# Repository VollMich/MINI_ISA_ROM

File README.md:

# MINI_ISA_ROM Card

the original design is from wiretap and it is awesome! He published it a while ago in a [thread on vogons](https://www.vogons.org/viewtopic.php?t=82499). Please do not get confused by my explanations further down. You don't need to understand binary logic to use this Rom adapter card. All you need to know is, that this is an exact copy of his design, except for the Jumper settings table on the silk screen , which has been corrected on this PCB, since wiretap's Jumper settings table was wrong. This PCB can be set according to the table on the card. This was the whole reason for this variant of wiretap's original design. You also need to know: Wiretap's original design is flawless and can be used without problems. It's just the settings table on the silk screen, that can give you a headache. You can use the jumper settings table from this project, to set up wiretap's card and you'll be fine. If you prefer to build a new one with a corrected silk screen, feel free to [download my gerbers](https://github.com/VollMich/MINI_ISA_ROM/raw/main/gerbers.zip).

## Why did i modify wiretap's awsome pcb design?
Wiretap's design is flawless except for the jumper table on the silk screen, which doesn't show the correct settings for the card. But his card works great otherwise. I built this version of his PCB to supply it with a proper silk screen. The complete list of possible Adresses is as follows:

|J1-J4|Base Address| Range | Validity | Usable? | Comment |
|-----|------------|-------|----------|---------|---------|
|0000|F800| F8000-FFFFF | INVALID | too high for option rom, DO NOT USE!||
|1000|F000| F0000-F7FFF | INVALID | too high for option rom, DO NOT USE!||
|0100|E800| E8000-EFFFF | INVALID | too high for option rom, DO NOT USE!||
|1100|E000| E0000-E7FFF | INVALID | too high for option rom, DO NOT USE!||
|**0010**|**D800**| **D8000-DFFFF** | **VALID**   | valid 32K block for a 27C256 Rom    || 
|**1010**|**D000**| **D0000-D7FFF** | **VALID**   | valid 32K block for a 27C256 Rom    ||
|**0110**|**C800**| **C8000-CFFFF** | **VALID**   | valid 32K block for a 27C256 Rom    | If you happen to have built AnotherMaker's version of this PCB, be aware, that there is a signal line missing between J2 on his PCB, this setting doesn't work on his card| 
|**1110**|**C000**| **C0000-C7FFF** | **VALID**   | valid 32K block for a 27C256 Rom    | VGA roms often start at C000. If you have a VGA card in your system, this range is probably occupied. If you happen to have built AnotherMaker's version of this PCB, be aware, that there is a signal line missing between J2 on his PCB, this setting doesn't work on his card.|  
|0001|B800| B8000-BFFFF | INVALID | too low for option rom, DO NOT USE! ||
|1001|B000| B0000-B7FFF | INVALID | too low for option rom, DO NOT USE! ||
|0101|A800| A8000-AFFFF | INVALID | too low for option rom, DO NOT USE! ||
|1101|A000| A0000-A7FFF | INVALID | too low for option rom, DO NOT USE! ||
|0011|9800| 98000-9FFFF | INVALID | too low for option rom, DO NOT USE! ||
|1011|9000| 90000-97FFF | INVALID | too low for option rom, DO NOT USE! ||
|0111|8800| 88000-8FFFF | INVALID | too low for option rom, DO NOT USE! ||
|1111|8000| 80000-87FFF | INVALID | too low for option rom, DO NOT USE! ||

There are really just four valid jumper settings out of sixteen possible combinations. All the other addresses wouldn't be recognized as option roms or even cause address conflicts with other resources. The reason is the huge rom size of 32K and the designers choice, to map the full size of the rom. The rom is directly attached to ADR0-ADR14 (which is 32K). With this low number of parts, it was kind of mandatory to use ADR15-ADR18 for address comparison. But only four combinations of J1-J4 wich are used to compare to ADR15-ADR18 end up in the address range for option roms, which is only 128K. There are only four 32K blocks possible in this range. Other cards can set more addresses, because they use smaller roms and hence, smaller blocks like 16K, 8K or even smaller. With this card you can use only one of four valid 32K blocks between C000 and DFFF. 

these are: 

|J1-J4|Base Address| Range | Block size |
|-----|------------|-------|------------|
|**0010**|**D800**| **D8000-DFFFF** | 32K|
|**1010**|**D000**| **D0000-D7FFF** | 32K|
|**0110**|**C800**| **C8000-CFFFF** | 32K|
|**1110**|**C000**| **C0000-C7FFF** | 32K|

## How does the address selection work?
The rom is directly connected to ADR0-ADR14 (32K). The Jumpers pins in the jumper block on this card are connected to ADR15-ADR18 left to right. The msb is on the right. The pins are pulled up to 5V by the 10K resistor network. If you set a jumper, the line is pulled down to 0V. The jumpers are connected as follows:

| Jumper (upper pin)| Signal Name| Connected to...| Used for...| Comment |
|-------------------|-----------|----------------|-------------|---------|
|J1                | P0        | 47LS688-PIN2   | pulled up via resistor network, to be compared to ADR15||
|J2                | P1        | 47LS688-PIN4   | pulled up via resistor network, to be compared to ADR16| Watch out if you got hold of AnotherMaker's version of this PCB on PCBWay. This line is missing on his layout, J2 is useless on his card.|
|J3                | P2        | 47LS688-PIN6   | pulled up via resistor network, to be compared to ADR17||
|J4                | P3        | 47LS688-PIN8   | pulled up via resistor network, to be compared to ADR18||

## OK, give me an example
This is the Address C0000, the base address of the memory range for option roms. It's binary representation is: 1100 0000 0000 0000 0000. if you write C0000 differently you get: 1 1000 000000000000000. The four separated bits on the left are connected to the jumper block from right to left. If you read it from right to left, you get 0001. There is one more step to do. You need to invert the value because a set jumper pulls the bit low. It's inverse logic. 
You get 1110. Hooray, this is the jumper setting for C0000.

## On writing a rom to this huge 32K chip (27C256). 
---------------------------------------------------------------------------------
If you just want to write a single rom to your chip, you can do so. Just make sure that your rom is aligned properly. Every rom has a header which contains the length of the rom. The length of the rom must be a multiple of 2K (it's 512B but there are some motherboards, that need the rom size to be a multiple of 2K, so it's best practice to follow this rule). If you downloaded a rom from xtide, it's probably not aligned. At least current binary downloads aren't. You need to run XTIDECFG.EXE to align the rom properly. The tool will pump up the size to the next 2K-border and calculate a proper 3-byte checksum at the end of the rom. Remember that you need to use the version of XTIDECFG.EXE, that was supplied with your roms. If you save the rom to a file, it is ready to be written with your eprom writer. When you are loading the file into your writer, you can select "Clear buffer when loading the file: Clear buffer with 0x00". The checksum does not have to be calculated again. The zeros at the end of the rom will be seen by your system and the range will be occupied, but only the first, properly aligned and properly checksummed area will be recognized as rom. And it will work fine. 

## On writing multiple roms on one chip
No one can stop you from loading multiple roms into the 32K of the 27c256. As long as you align them on 2K-adresses and supply the images with the correct headers and checksums, they will each be recognized as separate rom without a problem.

Happy retrocomputing ;)

Phonox

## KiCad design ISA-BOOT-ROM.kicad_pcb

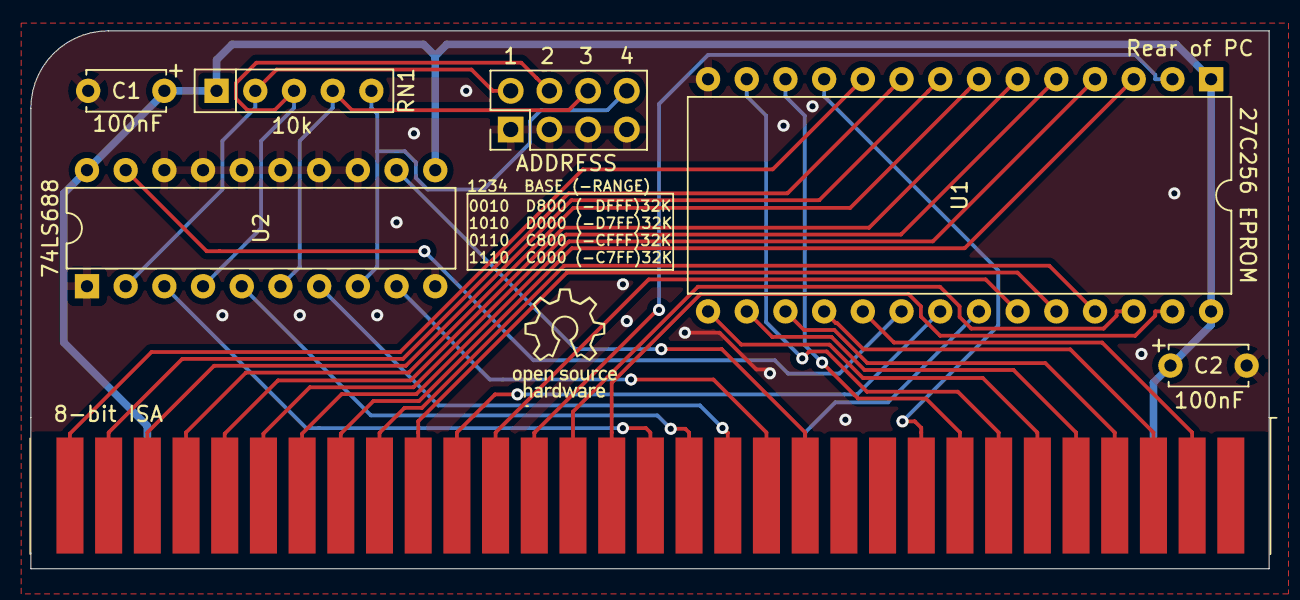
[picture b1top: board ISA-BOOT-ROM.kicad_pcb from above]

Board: 2 copper layers, 81.3 x 35.3 mm, 7 parts (0 on the bottom side), 36 nets.

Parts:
ADDRESS: Conn_02x04_Odd_Even; PinHeader_2x04_P2.54mm_Vertical
C1, C2: 100nF; C_Disc_D5.0mm_W2.5mm_P5.00mm
J1: Bus_ISA_8bit; BUS_XT
RN1: 10k; R_Array_SIP5
U1: 27C256; DIP-28_W15.24mm
U2: 74LS688; DIP-20_W7.62mm

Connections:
+5V: C1.1, C2.1, J1.3, J1.29, RN1.1, U1.1, U1.28, U2.11, U2.20
/ADR00: J1.62, U1.10
/ADR01: J1.61, U1.9
/ADR02: J1.60, U1.8
/ADR03: J1.59, U1.7
/ADR04: J1.58, U1.6
/ADR05: J1.57, U1.5
/ADR06: J1.56, U1.4
/ADR07: J1.55, U1.3
/ADR08: J1.54, U1.25
/ADR09: J1.53, U1.24
/ADR10: J1.52, U1.21
/ADR11: J1.51, U1.23
/ADR12: J1.50, U1.2
/ADR13: J1.49, U1.26
/ADR14: J1.48, U1.27
/ADR15: J1.47, U2.3
/ADR16: J1.46, U2.5
/ADR17: J1.45, U2.7
/ADR18: J1.44, U2.9
/ADR19: J1.43, U2.12
/CE: U1.20, U2.19
/DATA0: J1.40, U1.11
/DATA1: J1.39, U1.12
/DATA2: J1.38, U1.13
/DATA3: J1.37, U1.15
/DATA4: J1.36, U1.16
/DATA5: J1.35, U1.17
/DATA6: J1.34, U1.18
/DATA7: J1.33, U1.19
/MEMR: J1.12, U1.22
/P0: ADDRESS.2, RN1.2, U2.2
/P1: ADDRESS.4, RN1.3, U2.4
/P2: ADDRESS.6, RN1.4, U2.6
/P3: ADDRESS.8, RN1.5, U2.8
GND: ADDRESS.1, ADDRESS.3, ADDRESS.5, ADDRESS.7, C1.2, C2.2, J1.1, J1.10, J1.31, U1.14, U2.1, U2.10, U2.13, U2.14, U2.15, U2.16, U2.17, U2.18
